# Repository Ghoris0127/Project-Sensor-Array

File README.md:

# Project Minor Embedded Systems Sensor Array
 Code for minor Embedded System project Sensor Array

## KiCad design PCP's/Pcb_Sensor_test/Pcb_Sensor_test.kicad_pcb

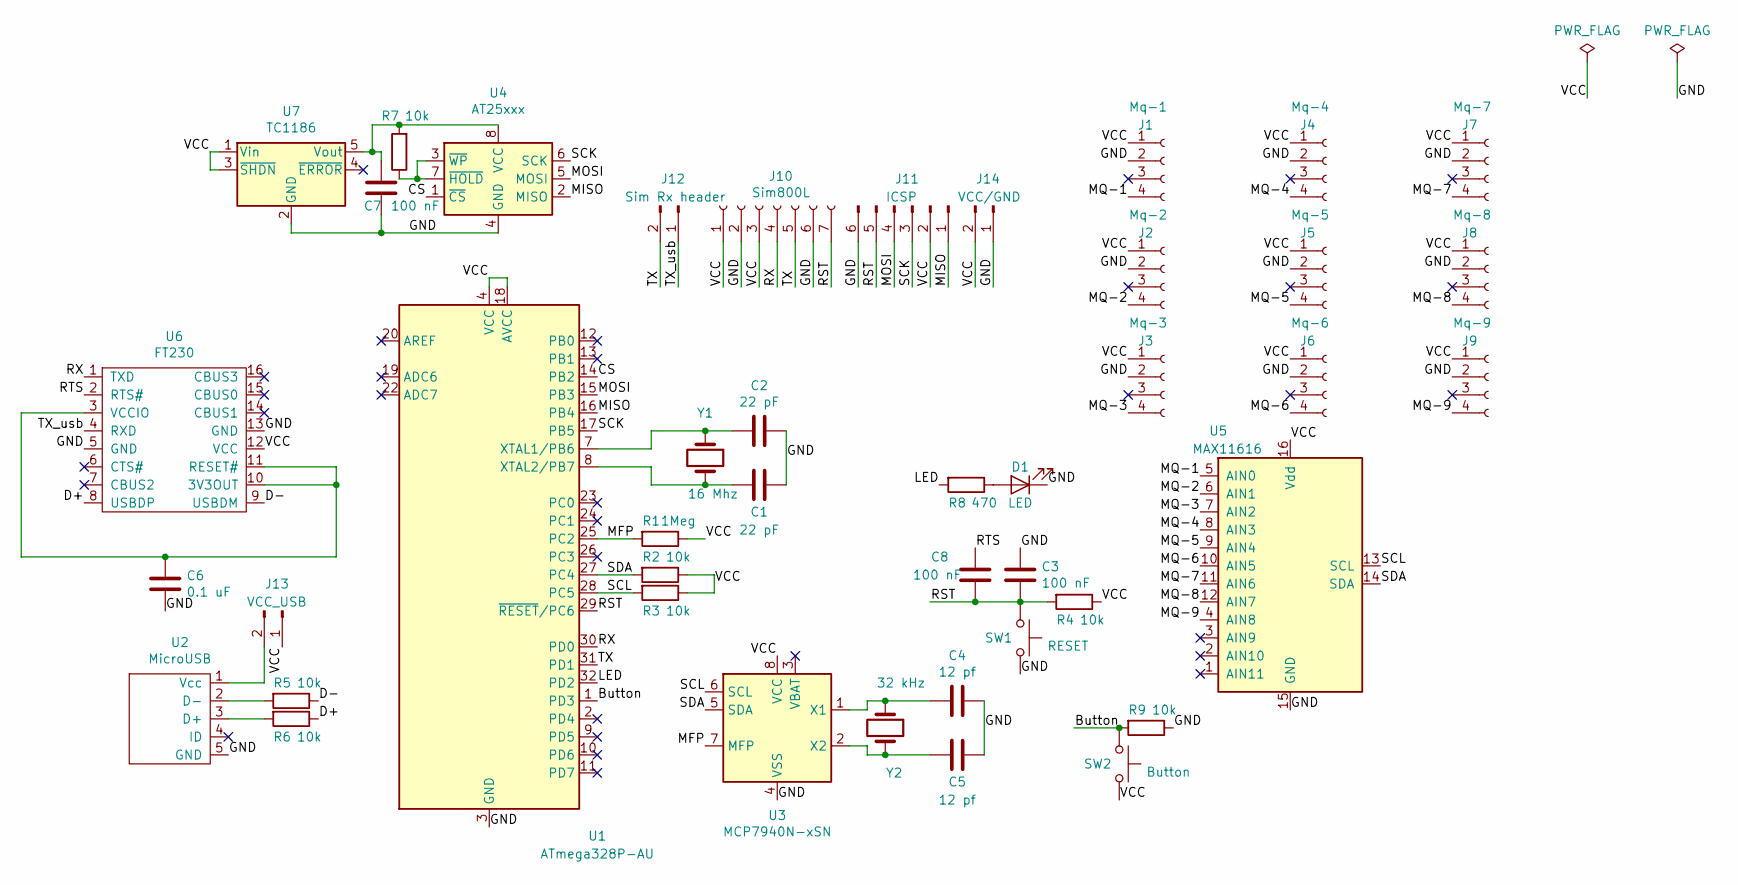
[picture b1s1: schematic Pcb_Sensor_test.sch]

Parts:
C1, C2: 22 pF; C_1206_3216Metric_Pad1.42x1.75mm_HandSolder
C3, C7, C8: 100 nF; C_1206_3216Metric_Pad1.42x1.75mm_HandSolder
C4, C5: 12 pf; C_1206_3216Metric_Pad1.42x1.75mm_HandSolder
C6: 0.1 uF; C_1206_3216Metric_Pad1.42x1.75mm_HandSolder
D1: LED; LED_1206_3216Metric_Pad1.42x1.75mm_HandSolder
J1: Mq-1; PinHeader_1x04_P2.54mm_Vertical
J2: Mq-2; PinHeader_1x04_P2.54mm_Vertical
J3: Mq-3; PinHeader_1x04_P2.54mm_Vertical
J4: Mq-4; PinHeader_1x04_P2.54mm_Vertical
J5: Mq-5; PinHeader_1x04_P2.54mm_Vertical
J6: Mq-6; PinHeader_1x04_P2.54mm_Vertical
J7: Mq-7; PinHeader_1x04_P2.54mm_Vertical
J8: Mq-8; PinHeader_1x04_P2.54mm_Vertical
J9: Mq-9; PinHeader_1x04_P2.54mm_Vertical
J10: Sim800L; PinHeader_1x07_P2.54mm_Vertical
J11: ICSP; PinHeader_2x03_P2.54mm_Vertical
J12: Sim Rx header; PinSocket_1x02_P2.54mm_Vertical
J13: VCC_USB; PinSocket_1x02_P2.54mm_Vertical
J14: VCC/GND; TerminalBlock_RND_205-00287_1x02_P5.08mm_Horizontal
R1: 1Meg; R_1206_3216Metric_Pad1.42x1.75mm_HandSolder
R2, R3, R4, R5, R6, R7, R9: 10k; R_1206_3216Metric_Pad1.42x1.75mm_HandSolder
R8: 470; R_1206_3216Metric_Pad1.42x1.75mm_HandSolder
SW1: RESET; SW_Tactile_Straight_KSA0Axx1LFTR
SW2: Button; SW_Tactile_Straight_KSA0Axx1LFTR
U1: ATmega328P-AU; TQFP-32_7x7mm_P0.8mm
U2: MicroUSB; USB_Micro-B_Molex-105017-0001
U3: MCP7940N-xSN; SOIC-8_3.9x4.9mm_P1.27mm
U4: AT25xxx; SOIC-8_3.9x4.9mm_P1.27mm
U5: MAX11616; QSOP-16_3.9x4.9mm_P0.635mm
U6: FT230; SSOP-16_3.9x4.9mm_P0.635mm
U7: TC1186; SOT-23-5_HandSoldering
Y1: 16 Mhz; Crystal_SMD_Abracon_ABM7-2Pin_6.0x3.5mm
Y2: 32 kHz; Crystal_SMD_2012-2Pin_2.0x1.2mm_HandSoldering

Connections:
/Button: R9.2, SW2.1, U1.1 (PD3)
/CS: U1.14 (PB2), U4.1 (~CS)
/D+: R6.1, U6.8 (USBDP)
/D-: R5.1, U6.9 (USBDM)
/GND: C1.1, C2.1, C3.1, C4.1, C5.1, C6.2, C7.2, D1.1 (K), J1.2, J2.2, J3.2, J4.2, J5.2, J6.2, J7.2, J8.2, J9.2, J10.2, J10.6, J11.6, J14.1, R9.1, SW1.2, U1.3 (GND), U1.5 (GND), U1.21 (GND), U2.5 (GND), U3.4 (VSS), U4.4 (GND), U5.15 (GND), U6.5 (GND), U6.13 (GND), U7.2 (GND)
/LED: R8.2, U1.32 (PD2)
/MFP: R1.2, U1.25 (PC2), U3.7 (MFP)
/MISO: J11.1, U1.16 (PB4), U4.2 (MISO)
/MOSI: J11.4, U1.15 (PB3), U4.5 (MOSI)
/MQ-1: J1.4, U5.5 (AIN0)
/MQ-2: J2.4, U5.6 (AIN1)
/MQ-3: J3.4, U5.7 (AIN2)
/MQ-4: J4.4, U5.8 (AIN3)
/MQ-5: J5.4, U5.9 (AIN4)
/MQ-6: J6.4, U5.10 (AIN5)
/MQ-7: J7.4, U5.11 (AIN6)
/MQ-8: J8.4, U5.12 (AIN7)
/MQ-9: J9.4, U5.4 (AIN8)
/RST: C3.2, C8.2, J10.7, J11.5, R4.2, SW1.1, U1.29 (~RESET~/PC6)
/RTS: C8.1, U6.2 (RTS#)
/RX: J10.4, U1.30 (PD0), U6.1 (TXD)
/SCK: J11.3, U1.17 (PB5), U4.6 (SCK)
/SCL: R3.2, U1.28 (PC5), U3.6 (SCL), U5.13 (SCL)
/SDA: R2.2, U1.27 (PC4), U3.5 (SDA), U5.14 (SDA)
/TX: J10.5, J12.2, U1.31 (PD1)
/TX_usb: J12.1, U6.4 (RXD)
/VCC: J1.1, J2.1, J3.1, J4.1, J5.1, J6.1, J7.1, J8.1, J9.1, J10.1, J10.3, J11.2, J13.1, J14.2, R1.1, R2.1, R3.1, R4.1, SW2.2, U1.4 (VCC), U1.6 (VCC), U1.18 (AVCC), U3.8 (VCC), U5.16 (Vdd), U6.12 (VCC), U7.1 (Vin), U7.3 (~SHDN)
unnamed: C1.2, U1.8 (XTAL2/PB7), Y1.2
unnamed: C2.2, U1.7 (XTAL1/PB6), Y1.1
unnamed: C4.2, U3.1 (X1), Y2.1
unnamed: C5.2, U3.2 (X2), Y2.2
unnamed: C6.1, U6.3 (VCCIO), U6.10 (3V3OUT), U6.11 (RESET#)
unnamed: C7.1, R7.2, U4.8 (VCC), U7.5 (Vout)
unnamed: D1.2 (A), R8.1
unnamed: J13.2, U2.1 (Vcc)
unnamed: R5.2, U2.2 (D-)
unnamed: R6.2, U2.3 (D+)
unnamed: R7.1, U4.3 (~WP), U4.7 (~HOLD)

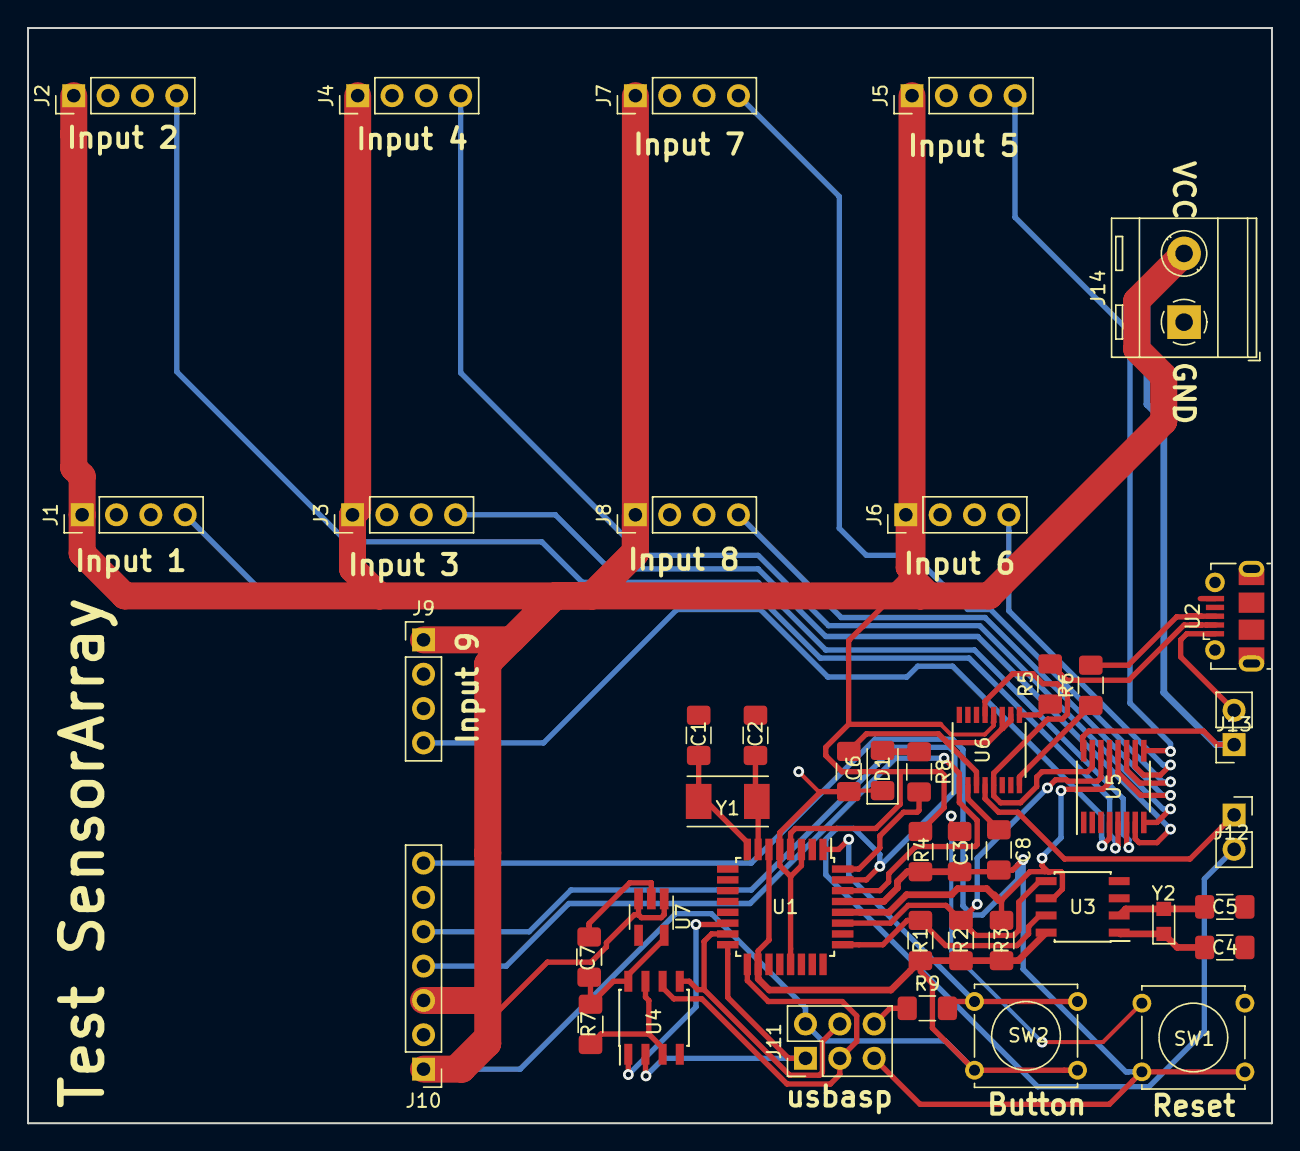
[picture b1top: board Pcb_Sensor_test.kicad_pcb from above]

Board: 2 copper layers, 92.0 x 81.0 mm, 43 parts (0 on the bottom side), 38 nets.

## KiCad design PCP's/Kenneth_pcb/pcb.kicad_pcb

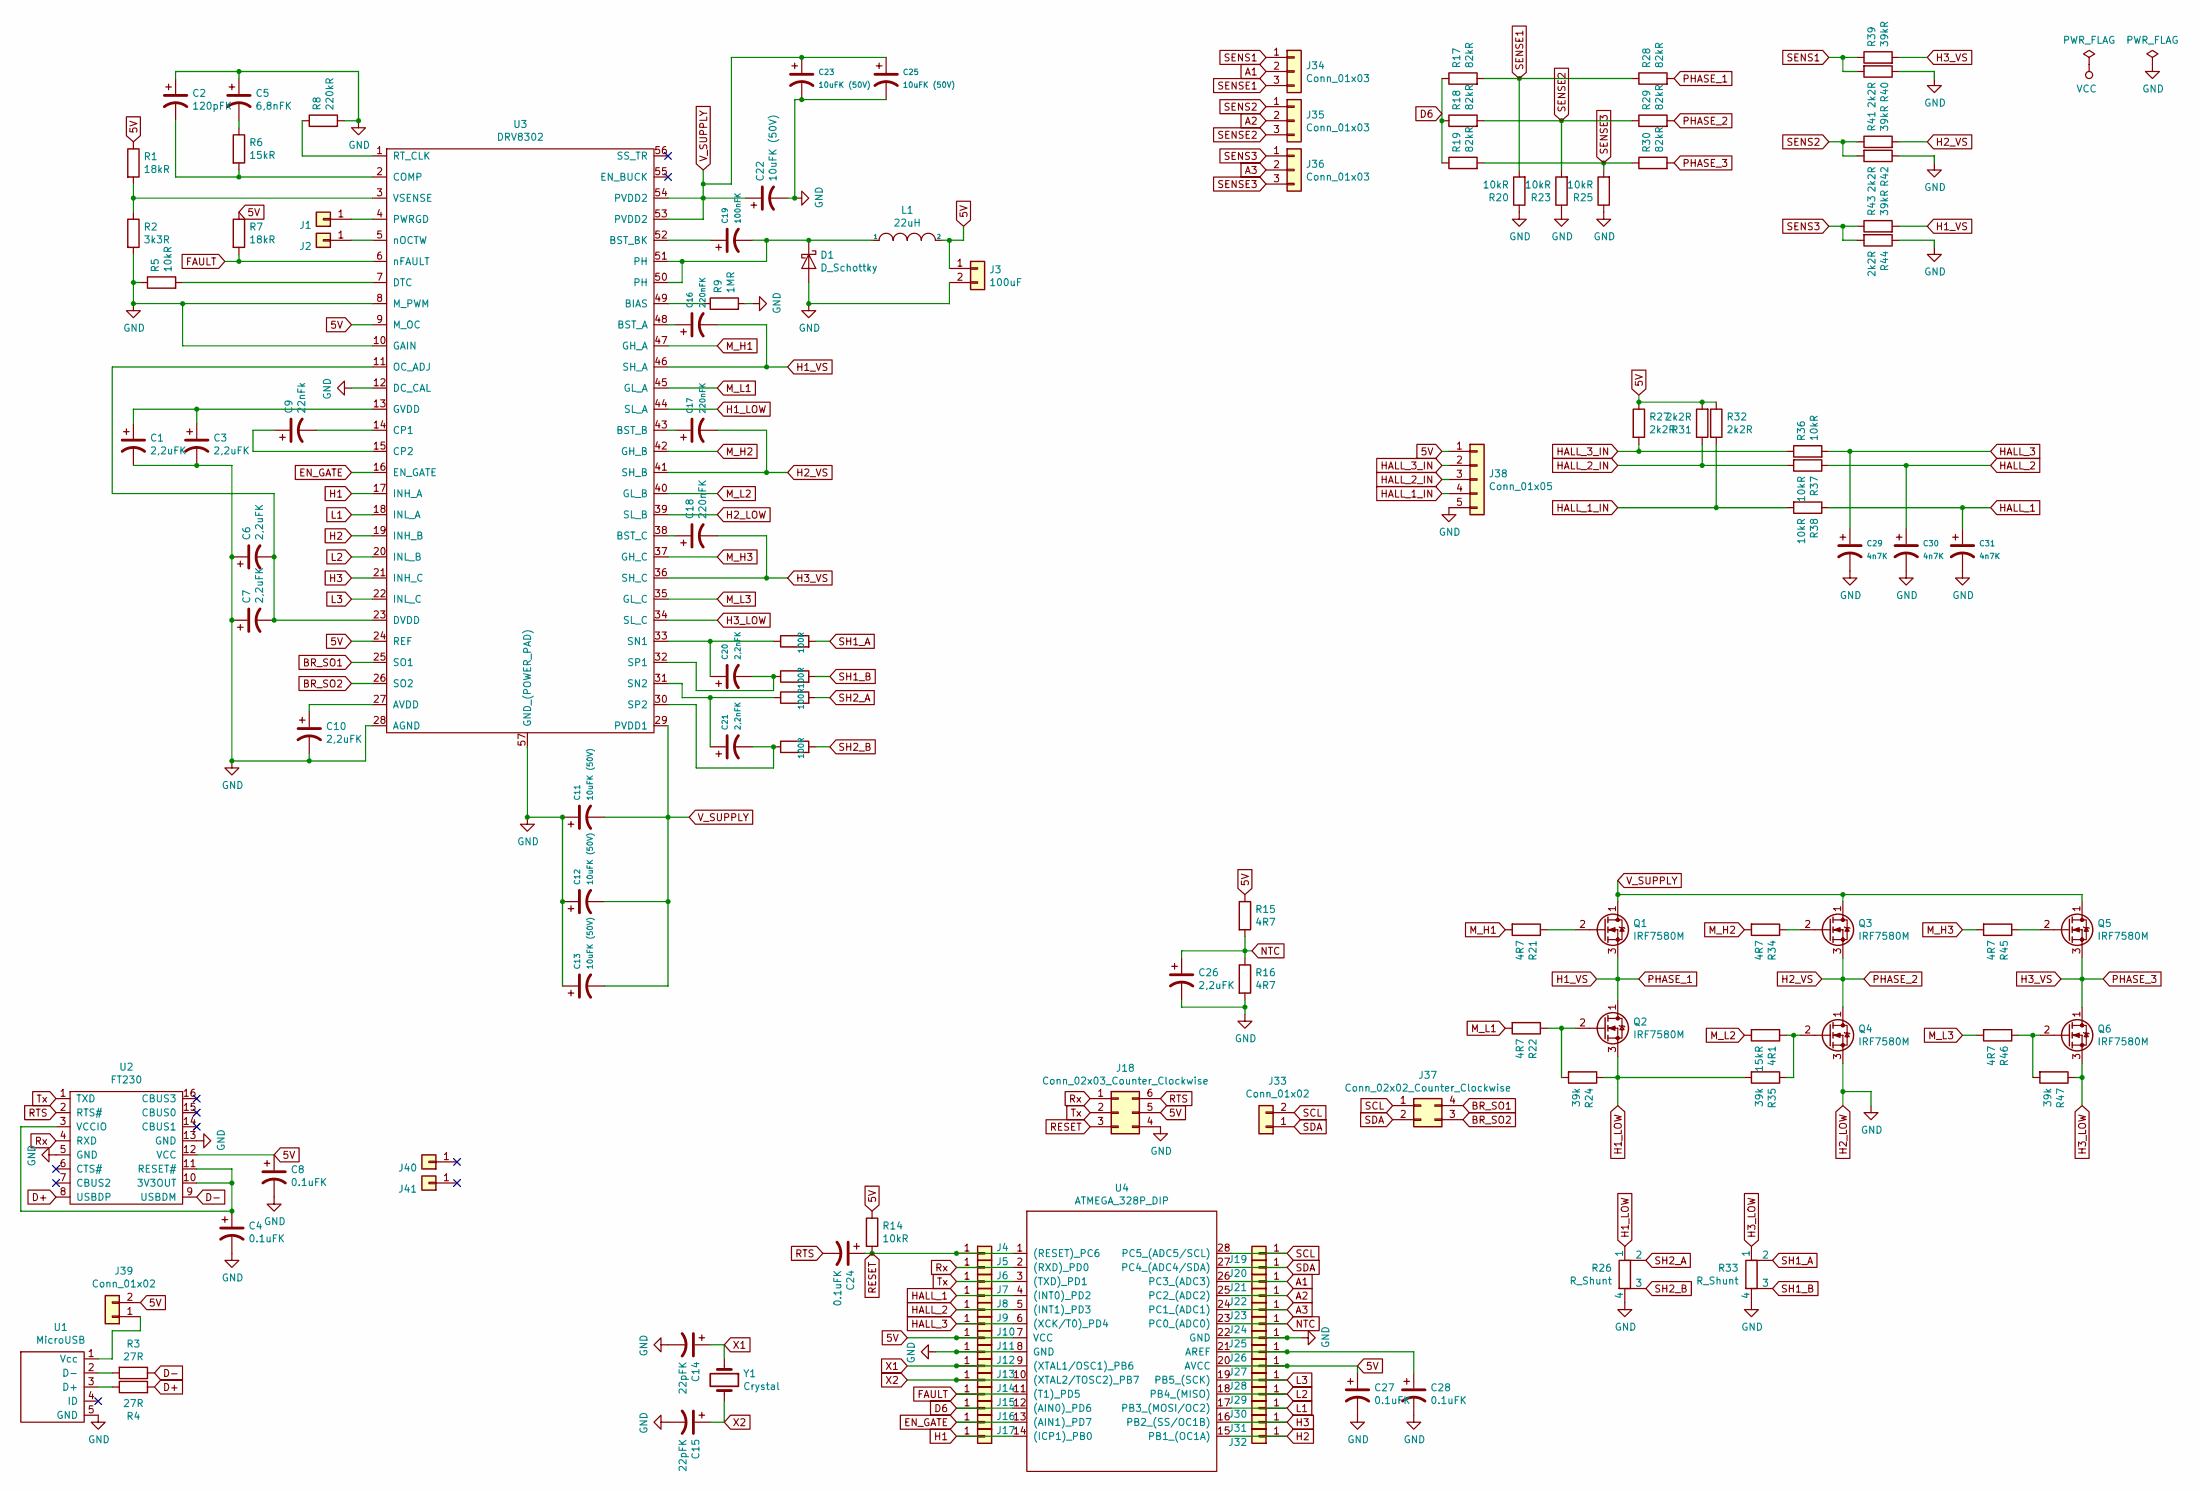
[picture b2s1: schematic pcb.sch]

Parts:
4R1: 15kR; R_0805_HandSoldering
C1, C3, C6, C7, C10, C26: 2,2uFK; C_0805_HandSoldering
C2: 120pFK; C_0805_HandSoldering
C4, C8, C24, C27, C28: 0.1uFK; C_0805_HandSoldering
C5: 6,8nFK; C_0805_HandSoldering
C9: 22nFk; C_0805_HandSoldering
C11, C12, C13, C22, C23, C25: 10uFK (50V); C_1206_HandSoldering
C14, C15: 22pFK; C_0805_HandSoldering
C16, C17, C18: 220nFK; C_0805_HandSoldering
C19: 100nFK; C_0805_HandSoldering
C20, C21: 2,2nFK; C_0805_HandSoldering
C29, C30, C31: 4n7K; C_0805_HandSoldering
D1: D_Schottky; D_SOD-123F
J1, J2, J4, J5, J6, J7, J8, J9, J10, J11, J12, J13, J14, J15, J16, J17, J19, J20, J21, J22, J23, J24, J25, J26, J27, J28, J29, J30, J31, J32, J40, J41: Conn_01x01; PinHeader_1x01_P2.54mm_Vertical
J3: 100uF; PinHeader_1x02_P2.54mm_Vertical
J18: Conn_02x03_Counter_Clockwise; PinHeader_2x03_P2.54mm_Vertical
J33, J39: Conn_01x02; PinHeader_1x02_P2.54mm_Vertical
J34, J35, J36: Conn_01x03; PinHeader_1x03_P2.54mm_Vertical
J37: Conn_02x02_Counter_Clockwise; PinHeader_2x02_P2.54mm_Vertical
J38: Conn_01x05; PinHeader_1x05_P2.54mm_Vertical
L1: 22uH; SDR0805
Q1, Q2, Q3, Q4, Q5, Q6: IRF7580M; IRFS7530
R1, R7: 18kR; R_0805_HandSoldering
R2: 3k3R; R_0805_HandSoldering
R3, R4: 27R; R_0805_HandSoldering
R5, R14, R20, R23, R25, R36, R37, R38: 10kR; R_0805_HandSoldering
R6: 15kR; R_0805_HandSoldering
R8: 220kR; R_0805_HandSoldering
R9: 1MR; R_0805_HandSoldering
R10, R11, R12, R13: 100R; R_0805_HandSoldering
R15: 4R7; R_0603_HandSoldering
R16, R21, R22, R34, R45, R46: 4R7; R_0805_HandSoldering
R17, R18, R19, R28, R29, R30: 82kR; R_0805_HandSoldering
R24, R35, R47: 39k; R_0805_HandSoldering
R26, R33: R_Shunt; WSLP2726
R27, R31, R32, R40, R42, R44: 2k2R; R_0805_HandSoldering
R39, R41, R43: 39kR; R_0805_HandSoldering
U1: MicroUSB; USB_Micro-B_Molex-105017-0001
U2: FT230; SSOP-16_3.9x4.9mm_Pitch0.635mm
U3: DRV8302
U4: ATMEGA_328P_DIP; DIP-28_W7.62mm_Socket_LongPads
Y1: Crystal; Resonator-2Pin_W6.0mm_H3.0mm

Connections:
5V: C8.1, C27.1, J3.1, J10.1, J18.5, J27.1, J38.1, J39.2, L1.2, R1.1, R7.1, R14.1, R15.1, R27.1, R31.2, R32.1, U2.12 (VCC), U3.9 (M_OC), U3.24 (REF), U4.7 (VCC), U4.20 (AVCC)
A1: J21.1, J34.2, U4.26 (PC3_(ADC3))
A2: J22.1, J35.2, U4.25 (PC2_(ADC2))
A3: J23.1, J36.2, U4.24 (PC1_(ADC1))
BR_SO1: J37.4, U3.25 (SO1)
BR_SO2: J37.3, U3.26 (SO2)
D6: J15.1, R17.1, R18.1, R19.1, U4.12 ((AIN0)_PD6)
D+: R4.2, U2.8 (USBDP)
D-: R3.1, U2.9 (USBDM)
EN_GATE: J16.1, U3.16 (EN_GATE), U4.13 ((AIN1)_PD7)
FAULT: J14.1, R7.2, U3.6 (nFAULT), U4.11 ((T1)_PD5)
H1: J17.1, U3.17 (INH_A), U4.14 ((ICP1)_PB0)
H1_LOW: Q2.3 (S), R24.1, R26.1, R35.2, U3.44 (SL_A)
H1_VS: C16.2, Q1.3 (S), Q2.1 (D), R28.2, R43.2, U3.46 (SH_A)
H2: J32.1, U3.19 (INH_B), U4.15 (PB1_(OC1A))
H2_LOW: C1.2, C2.1, C3.2, C4.2, C5.1, C6.1, C7.1, C8.2, C10.2, C11.1, C12.1, C13.1, C14.2, C15.2, C22.2, C23.2, C25.2, C26.2, C27.2, C28.2, C29.2, C30.2, C31.2, D1.2 (A), J3.2, J11.1, J18.4, J25.1, J38.5, J41.1, Q4.3 (S), R2.2, R5.1, R8.2, R9.2, R16.2, R20.1, R23.1, R25.1, R26.4, R33.4, R40.1, R42.1, R44.1, U1.5 (GND), U2.5 (GND), U2.13 (GND), U3.8 (M_PWM), U3.10 (GAIN), U3.12 (DC_CAL), U3.28 (AGND), U3.39 (SL_B), U3.57 (GND_(POWER_PAD)), U4.8 (GND), U4.22 (GND)
H2_VS: C17.2, Q3.3 (S), Q4.1 (D), R29.2, R41.2, U3.41 (SH_B)
H3: J31.1, U3.21 (INH_C), U4.16 (PB2_(SS/OC1B))
H3_LOW: Q6.3 (S), R33.1, R47.1, U3.34 (SL_C)
H3_VS: C18.2, Q5.3 (S), Q6.1 (D), R30.2, R39.2, U3.36 (SH_C)
HALL_1: C31.1, J7.1, R38.1, U4.4 ((INT0)_PD2)
HALL_1_IN: J38.4, R32.2, R38.2
HALL_2: C30.1, J8.1, R37.1, U4.5 ((INT1)_PD3)
HALL_2_IN: J38.3, R31.1, R37.2
HALL_3: C29.1, J9.1, R36.2, U4.6 ((XCK/T0)_PD4)
HALL_3_IN: J38.2, R27.2, R36.1
L1: J30.1, U3.18 (INL_A), U4.17 (PB3_(MOSI/OC2))
L2: J29.1, U3.20 (INL_B), U4.18 (PB4_(MISO))
L3: J28.1, U3.22 (INL_C), U4.19 (PB5_(SCK))
M_H1: R21.2, U3.47 (GH_A)
M_H2: R34.2, U3.42 (GH_B)
M_H3: R45.2, U3.37 (GH_C)
M_L1: R22.2, U3.45 (GL_A)
M_L2: 4R1.2, U3.40 (GL_B)
M_L3: R46.2, U3.35 (GL_C)
NTC: C26.1, J24.1, R15.2, R16.1, U4.23 (PC0_(ADC0))
unnamed: 4R1.1, Q4.2 (G), R35.1
unnamed: C1.1, C3.1, U3.13 (GVDD)
unnamed: C2.2, R6.2, U3.2 (COMP)
unnamed: C4.1, U2.3 (VCCIO), U2.10 (3V3OUT), U2.11 (RESET#)
unnamed: C5.2, R6.1
unnamed: C6.2, C7.2, U3.11 (OC_ADJ), U3.23 (DVDD)
unnamed: C9.1, U3.15 (CP2)
unnamed: C9.2, U3.14 (CP1)
unnamed: C10.1, U3.27 (AVDD)
unnamed: C16.1, U3.48 (BST_A)
unnamed: C17.1, U3.43 (BST_B)
unnamed: C18.1, U3.38 (BST_C)
unnamed: C19.1, U3.52 (BST_BK)
unnamed: C19.2, D1.1 (K), L1.1, U3.50 (PH), U3.51 (PH)
unnamed: C20.1, R10.1, U3.33 (SN1)
unnamed: C20.2, R11.1, U3.32 (SP1)
unnamed: C21.1, R12.1, U3.31 (SN2)
unnamed: C21.2, R13.1, U3.30 (SP2)
unnamed: C28.1, J26.1, U4.21 (AREF)
unnamed: J1.1, U3.4 (PWRGD)
unnamed: J2.1, U3.5 (nOCTW)
unnamed: J39.1, U1.1 (Vcc)
unnamed: Q1.2 (G), R21.1
unnamed: Q2.2 (G), R22.1, R24.2
unnamed: Q3.2 (G), R34.1
unnamed: Q5.2 (G), R45.1
unnamed: Q6.2 (G), R46.1, R47.2
unnamed: R1.2, R2.1, U3.3 (VSENSE)
unnamed: R3.2, U1.2 (D-)
unnamed: R4.1, U1.3 (D+)
unnamed: R5.2, U3.7 (DTC)
unnamed: R8.1, U3.1 (RT_CLK)
unnamed: R9.1, U3.49 (BIAS)
RESET: C24.1, J4.1, J18.3, R14.2, U4.1 ((RESET)_PC6)
RTS: C24.2, J18.6, U2.2 (RTS#)
Rx: J5.1, J18.1, U2.4 (RXD), U4.2 ((RXD)_PD0)
SCL: J19.1, J33.2, J37.1, U4.28 (PC5_(ADC5/SCL))
SDA: J20.1, J33.1, J37.2, U4.27 (PC4_(ADC4/SDA))
SENS1: J34.1, R39.1, R40.2
SENS2: J35.1, R41.1, R42.2
SENS3: J36.1, R43.1, R44.2
SENSE1: J34.3, R17.2, R20.2, R28.1
SENSE2: J35.3, R18.2, R23.2, R29.1
SENSE3: J36.3, R19.2, R25.2, R30.1
SH1_A: R10.2, R33.2
SH1_B: R11.2, R33.3
SH2_A: R12.2, R26.2
SH2_B: R13.2, R26.3
Tx: J6.1, J18.2, U2.1 (TXD), U4.3 ((TXD)_PD1)
V_SUPPLY: C11.2, C12.2, C13.2, C22.1, C23.1, C25.1, J40.1, Q1.1 (D), Q3.1 (D), Q5.1 (D), U3.29 (PVDD1), U3.53 (PVDD2), U3.54 (PVDD2)
X1: C14.1, J12.1, U4.9 ((XTAL1/OSC1)_PB6), Y1.1
X2: C15.1, J13.1, U4.10 ((XTAL2/TOSC2)_PB7), Y1.2

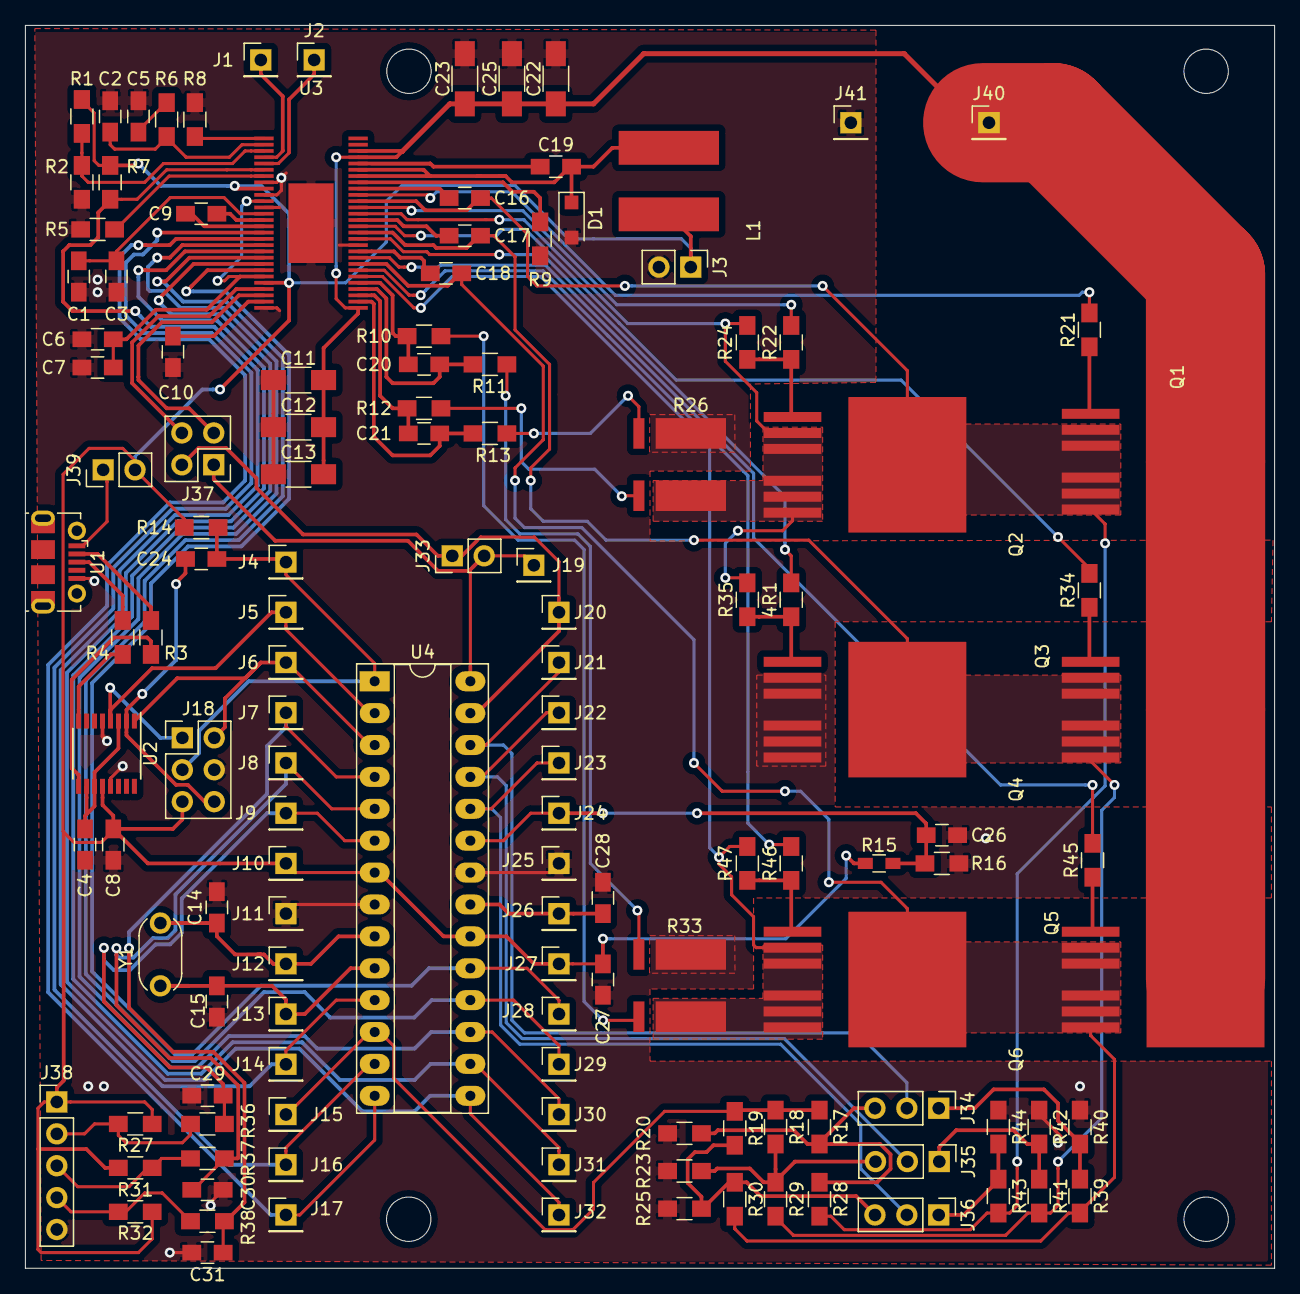
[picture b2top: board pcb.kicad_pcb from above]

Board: 2 copper layers, 99.5 x 99.0 mm, 133 parts (0 on the bottom side), 88 nets.

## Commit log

2019-09-13 Created folders to seperate code
2019-09-13 Created .gitignore, included visual studio
2019-09-13 Created VS project for web application
2019-09-13 Created example of webapp
2019-09-14 Researched how to develop .net ASP website
2019-09-15 Can show table of modules
2019-09-16 charts not working
2019-09-27 Renamed map module to sensorarray
2019-10-08 Removed C# project
2019-10-08 Started working on webapp
2019-10-21 Pcb erbij
